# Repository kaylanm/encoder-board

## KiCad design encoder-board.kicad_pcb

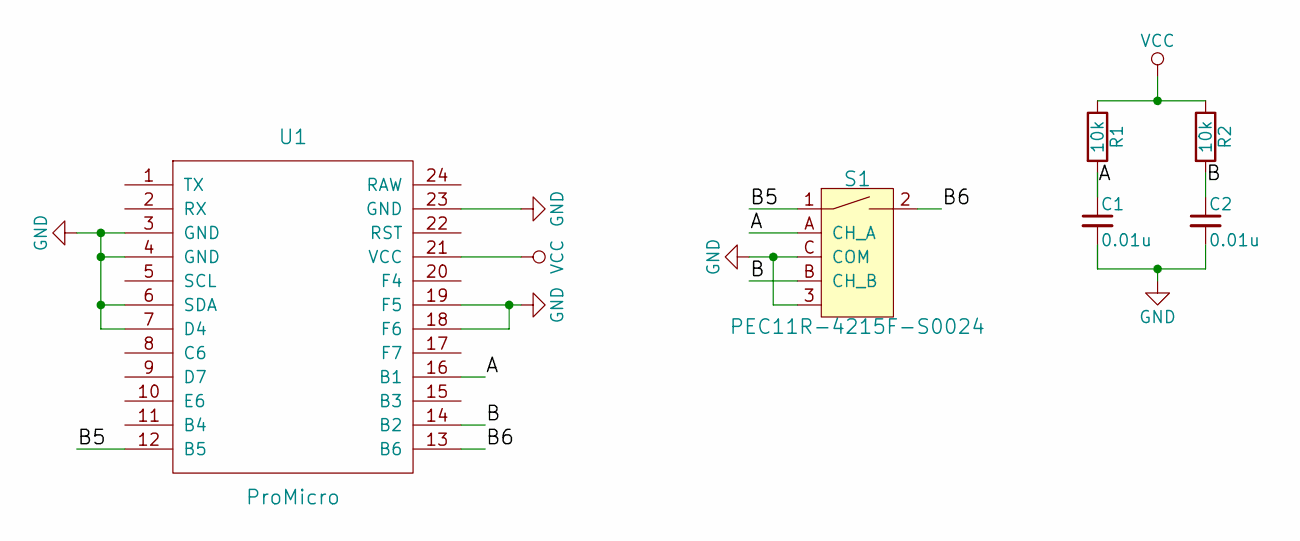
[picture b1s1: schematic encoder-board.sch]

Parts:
C1, C2: 0.01u; C_0805_HandSoldering
R1, R2: 10k; R_0805_HandSoldering
S1: PEC11R-4215F-S0024; Rotary_Encoder_Switched_PEC11R; MPN PEC11R-4215F-S0024; Digi-Key_PN PEC11R-4215F-S0024-ND
U1: ProMicro

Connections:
/A: C1.1, R1.2, S1.A (CH_A), U1.16 (B1)
/B: C2.1, R2.2, S1.B (CH_B), U1.14 (B2)
/B5: S1.1, U1.12 (B5)
/B6: S1.2, U1.13 (B6)
GND: C1.2, C2.2, S1.3, S1.C (COM), U1.3 (GND), U1.4 (GND), U1.6 (SDA), U1.7 (D4), U1.18 (F6), U1.19 (F5), U1.23 (GND)
VCC: R1.1, R2.1, U1.21 (VCC)

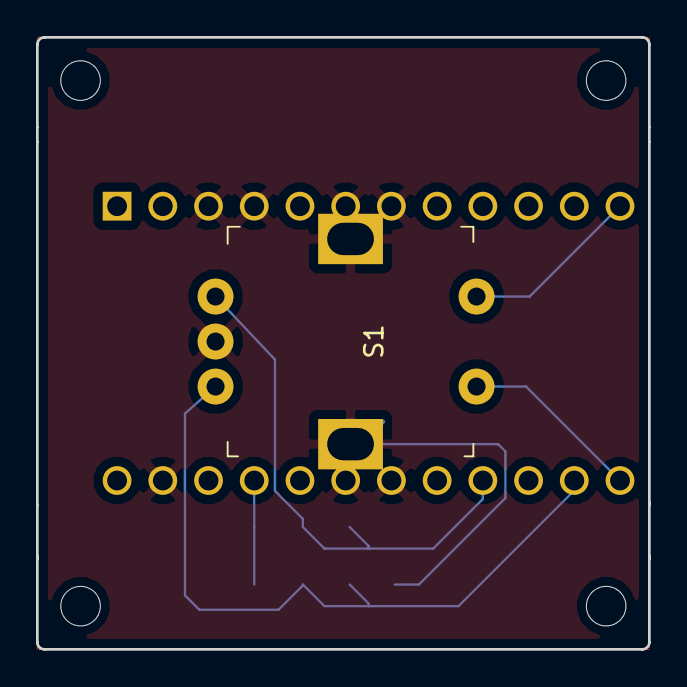
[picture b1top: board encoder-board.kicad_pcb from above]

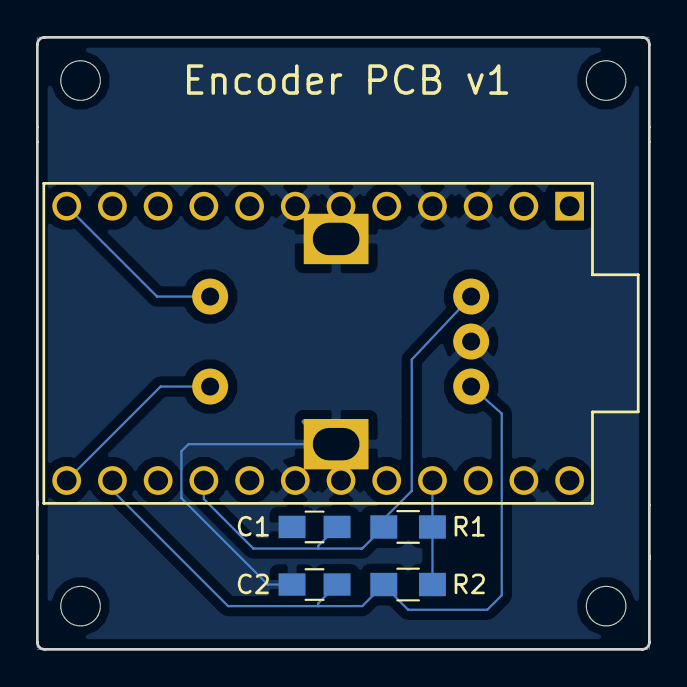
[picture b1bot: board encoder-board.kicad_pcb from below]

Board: 2 copper layers, 34.0 x 34.0 mm, 6 parts (5 on the bottom side), 6 nets.

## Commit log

2018-07-04 Initial commit.
